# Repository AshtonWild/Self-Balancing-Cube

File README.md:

# Self-Balancing-Cube

**UPDATE (2026-11-11)**

You can print redesigned cube https://www.thingiverse.com/thing:6695891

Folow this video https://youtu.be/ZU0oTBRDgOE

---

I created a PCB with KiCad, as it was cleaner than using a prototype board and provided GERBER files for PCB Manufacturing in "Gerber".  I used JLCPCB to have the PCB built.

All parts are available via Digikey or AliExpress.  

CPU: ESP32 DEVKIT v1 Type-C

Battery: 3S1P LiPo 500 mAH (11.1V)

Motor: Nidec 24H brushless motors (8 Pin Required)

Other: Regulator (L7805), Transistor 2N2222, 5V Active Buzzer, Capacitor 100uF / 0.1uF, Register 6.8k / 33k / 10k

All red connections not nescesary for this project! But if you are designing a PCB I recommend making these connections. Maybe I use encoders in the future, you will be able to use the new firmware without any changes.
 
How to build:

https://youtu.be/AJQZFHJzwt4

If something doesn't work, try the motors test sketch. It tests all motors, rotation directions and speeds. This helps you understand the problem is in software or in hardware.

ESP32 version also has an updated balancing point setting procedure. Important! In this video you can learn how to set the balancing points:

https://youtu.be/Nkm9PoihZOI

# Self-Balancing Cube Calibration Manual

Calibrate in this order: sensor check, motor test, edge, then vertex. Each stage depends on the one before it, and nothing is kept until you type `save`.

## Before you start

- **Firmware**: the cube's Arduino code (ESP32, based on remrc's Self-Balancing-Cube), including the `watch` command and the automatic MPU6050 re-wake.
- **Console over USB**: Arduino Serial Monitor at **115200 baud**, line ending set to **New Line**. With "No line ending", commands never run.
- **Console over Bluetooth**: pair with **ESP32-Cube** and use any serial terminal app.
- **Chaining**: several commands can go on one line, separated by `;` (for example `zK2 8; zK3 0.3`).
- **Unsaved changes are lost** on every reboot and every upload. Type `save` once something works.
- **Safety**: keep fingers clear of the wheels. They can kick hard when balancing starts or a gain is wrong. Type `stop` at any time to brake the wheels, and `start` to re-enable them.

## Step 1: Power up and check the sensor

The sensor must give live readings before any calibration means anything. Our first vertex calibration was recorded while it read all zeros.

1. Power up with the cube **lying still**. The blue LED stays on for about 1 s while the gyro zeroes.  
   If the console says the cube moved, keep it still and type `gyrocal`.
2. Type `watch` (or `w`). You get a live line about 4 times a second, starting with `raw X … Y … Z …`.
3. Tilt the cube by hand. All three raw values must change. Lying flat, one of them reads about ±16384 (1 g).
4. Type `w off` to stop the live view.

If the raw values are all 0: the MPU6050 is powered but asleep, usually because it wasn't connected at boot. Type `reboot` with the cube still. The firmware now also re-wakes the sensor by itself and prints `MPU6050 found - woken up and configured`.

If you see `IMU read errors - check the MPU6050 wiring`: check SDA on GPIO 21, SCL on GPIO 22, VCC and GND, and that AD0 is low (address 0x68). If errors only appear when the motors run, keep the I2C wires short and away from the motor wires.

## Step 2: Check the battery and motors

1. **Battery (once)**: measure the pack with a multimeter and type the reading, for example `vcal 11.8`. This makes the battery value in `s` and the low-battery alarm (8 to 9.5 V) correct.  
   A 3S pack below about 11 V gives the wheels less top speed, so the cube falls sooner.
2. **Motors**: lay the cube on a side so the wheels spin freely, then type `mtest`. Each wheel spins for 0.6 s.  
   - **OK** for all three: continue.  
   - **encoder counts backwards**: swap `ENCx_1` and `ENCx_2` for that motor in the PINS section and re-upload.  
   - **not spinning**: check the battery and the BRAKE, DIR, PWM and encoder wiring.  
   Type `stop` at any point to abort the test and brake the wheels.

Don't continue until all three motors pass.

## Step 3: Calibrate the edge

The edge uses one motor (motor 3) and one tilt axis, so it's the easiest place to start. The original gains, eK1 190 and eK2 31, were correct: don't flip their signs.

1. Check the gains: type `eK1` and `eK2`. They should read 190 and 31. If not, type `defaults` (this keeps your calibration).
2. Record the balance point: type `cal e`. During the 3 s countdown, stand the cube on its edge and hold it lightly where it would fall neither way.  
   Run `watch` during the countdown to see the check: `|X|` must be 7000 to 10000 and `|Y|` below 2000, both marked `ok`.  
   Blue LED on = right position. Fast flicker = wrong position.  
   Hold still while it samples (about 1.5 s). LED on for 2 s = accepted; flicker = rejected, and the console says why.
3. Give it room: type `fall 10` so it doesn't cut out at 7° while you tune. Optionally type `arme 1` to make it start more easily.
4. Let it balance: stand it on the same edge. The console prints `Balancing on EDGE`.
5. Tune if it rocks: a slow, growing rock means it needs more damping. Change eK2 one step at a time and leave eK1 alone.  
   - Rocking gets smaller: keep going.  
   - Buzzing or jittering: one step too far, so back off.
6. Trim: while it balances on its own, type `autotrim` and don't touch it for about 9 s. Run it a second time. Our result was `te = −1.09`.
7. Save: type `save`. Then `reboot` and check it still balances on the edge.

## Step 4: Calibrate the vertex

The vertex worked with the original gains too: K1 180, K2 30, zK2 8, zK3 0.3. The step that fixed it was setting the balance-point trims by hand while watching the live tilt.

1. Check the gains: type `K1`, `K2`, `zK2` and `zK3`. They should read 180, 30, 8 and 0.3.
2. Record the balance point: type `cal v`. During the countdown, stand the cube on its corner and hold it lightly at its balance point.  
   In `watch`, `|X|` and `|Y|` must both be below 2000 and marked `ok`. The rotation must stay under 15 deg/s while it samples.
3. Make starting easier: type `armv 1`. With the default 0.4° window, it's very hard to start by hand.
4. Measure the offset with the motors off: type `stop`, then `watch`. Hold the cube at the point where it really balances (it would fall equally either way). Read the line, for example `vertex tilt X +2.10 off, Y -1.30 off`.
5. Set the trims: type `tvx` and `tvy` to see the current values. Add the readings to them: with both at 0 and the example above, that's `tvx 2.1; tvy -1.3`.
6. Check: at the real balance point, `watch` should now read close to `X +0.00 ok, Y +0.00 ok`.
7. Balance: type `start`, hold it at the balance point, and let go when it takes over. The console prints `Balancing on VERTEX`.
8. Trim: while it balances, run `autotrim` twice (about 9 s each, hands off).
9. Save: type `save`, then `reboot` and check both the corner and the edge still balance.

## Troubleshooting

Most problems we hit were the balance point or the sensor, not the gains. Change one thing at a time.

| Symptom | Cause | Fix |
|---------|-------|-----|
| Raw X, Y, Z all read 0 | MPU6050 asleep (not connected at boot) | `reboot` with the cube still |
| IMU read errors | I2C wiring or noise | Check SDA 21, SCL 22, power, AD0; short wires away from motors |
| Motors never start | Tilt outside armv / arme, motors stopped, or not calibrated | Read the `watch` line; `armv 1`, `start`, or `cal v` / `cal e` |
| `watch` never shows vertex tilt | Raw \|X\| at the corner is 2000 or more | Redo `cal v`; send the raw values if it persists |
| Falls at the real balance point, starts only when tilted further | Zero point recorded in the wrong spot | Set `tvx` / `tvy` by hand (Step 4) |
| Slow rock that grows until it falls | Too little damping | Nudge eK2 (edge) or K2 (vertex) one step at a time |
| Buzzing or fast jitter | Gains too high | Back off one step; try `dlpf 3` |
| Balances, then the wheels speed up and it falls | Small balance-point offset; wheels hit full speed | `autotrim`; or watch `ix` / `iy` in `tel 20` and nudge the trim until flat |
| Cube spins faster and faster around its vertical axis | Yaw gains wrong | Keep `zK2 8`; try `zK3 0.4` or `0.2`. `zK2 -8` made it much worse |
| Gains seem to change by themselves | Not saved before a reboot or upload | `save` after every change you want to keep |
| A command prints nothing | Line ending, baud, or output scrolled past | New Line, 115200, `w off`; `tel off`; type a name alone, e.g. `eK1` |

Flipping the gain signs (negative eK1 / eK2 or K1 / K2) did not help on this cube: the original positive values are correct.

## Reference

Working settings on this cube. Type `p` for the full list. Gains marked "default" come back with `defaults`; the others are saved with `save` only.

| Setting | Value | Notes |
|---------|-------|-------|
| eK1 / eK2 | 190 / 31 | Edge gains, default |
| te | −1.09 | Edge trim from `autotrim` |
| K1 / K2 | 180 / 30 | Vertex gains, default |
| zK2 / zK3 | 8 / 0.3 | Yaw gains, default |
| tvx / tvy | from Step 4 | Vertex trims, set by hand then `autotrim` |
| armv | 1 | Default 0.4; reset by `defaults` |
| fall | 10 | Default 7; set back with `fall 7` if you like |

## Console menu explained

Type `help` to show the menu on the cube. Commands aren't case-sensitive, short forms are in brackets, and `help <topic>` (for example `help cal` or `help K1`) gives more detail on any item.

### Info

| Command | What it does |
|---------|--------------|
| `help` (`?`, `menu`) | Shows the menu. `help <topic>` explains one command or setting in detail. |
| `help leds` | Explains the blue LED blink patterns and RGB colours (table below). |
| `status` (`s`) | One-screen health check: mode (IDLE, VERTEX or EDGE), motors enabled or stopped, which position the cube is in, battery volts, angles, raw sensor values, wheel speeds and loop timing. Worst period should stay near 15000 us; late and I2C errors should stay at 0. |
| `params` (`p`) | Lists every tunable value, its current setting and what it does. Says if there are unsaved changes. |
| `tel [hz]` / `tel off` | Streams live data for the Arduino Serial Plotter (Tools > Serial Plotter). Default 20 Hz, maximum 66; keep it at 20 Hz or less over Bluetooth. Fields: m mode (0 idle, 1 vertex, 2 edge), ax ay tilt angle, gx gy tilt rate, w1–w3 wheel speeds, px py pz motor output (−255 to 255), ix iy wheel-position term. A steady ramp in ix or iy means the balance point is off. |
| `watch [hz]` (`w`) / `w off` | Readable live guide, default 4 Hz. Shows the raw sensor values and what's in or out of range: the calibration windows during `cal`, or the tilt from the balance point and the start window otherwise. Notes `[motors STOPPED]` when the wheels are off. |

### Setup and calibration

| Command | What it does |
|---------|--------------|
| `mtest` | Motor and encoder test, about 3 s. Lay the cube on a side first. Spins each wheel for 0.6 s and reports OK, backwards (swap that motor's encoder pins) or not spinning (check power and wiring). Won't start while the motors are stopped; `stop` aborts it. |
| `cal v [sec]` | Records the vertex balance point after a countdown (default 3 s). Needs raw \|X\| and \|Y\| below 2000 and rotation under 15 deg/s. Resets the vertex trims to 0. |
| `cal e [sec]` | Records the edge balance point the same way. Needs raw \|X\| of 7000 to 10000 and \|Y\| below 2000. Resets the edge trim to 0. |
| `autotrim` | Run while the cube balances on its own. Averages the lean for about 9 s and moves the trims (`tvx` / `tvy` on the vertex, `te` on the edge) to the real balance point. Run it twice, then `save`. Aborts if the cube stops balancing. |
| `gyrocal [sec]` | Re-zeroes the gyro (also done automatically at power-up). Keep the cube still; rejected if it moves. Use it if the angle drifts while the cube sits still. |
| `vcal <volts>` | Type a multimeter reading of the battery, e.g. `vcal 11.8`, to make the battery value and low-battery alarm correct. Rejects readings that don't make sense (for example a disconnected divider). |
| `buzz` | Two-part buzzer test. Test 1 (steady on): an active buzzer beeps. Test 2 (2 kHz tone): a passive buzzer beeps. The project needs an active 5 V buzzer. Silent in both: check polarity, 5 V and the transistor on GPIO 27. |

### Tuning

| Command | What it does |
|---------|--------------|
| `<name> <value>` | Sets a value, e.g. `K1 185`. Also works as `set K1 185` or `K1=185`. Values outside the allowed range are limited. |
| `<name>` | Prints one value, e.g. `eK2`. |
| `<name>+` / `<name>-` | Nudges a value by one step; repeat the sign for more steps (`eK3+++`). |

| Setting | What it controls | Default | Range (step) |
|---------|------------------|---------|--------------|
| K1 | Vertex: angle gain | 180 | −2000 to 2000 (5) |
| K2 | Vertex: tilt-rate gain (damping) | 30 | −500 to 500 (1) |
| K3 | Vertex: wheel-speed gain | 1.6 | −50 to 50 (0.1) |
| K4 | Vertex: wheel-position gain | 0.008 | −1 to 1 (0.001) |
| zK2 | Vertex: yaw-rate gain (stops turning) | 8 | −100 to 100 (0.5) |
| zK3 | Vertex: yaw wheel-speed gain | 0.3 | −10 to 10 (0.05) |
| eK1 | Edge: angle gain | 190 | −2000 to 2000 (5) |
| eK2 | Edge: tilt-rate gain (damping) | 31 | −500 to 500 (1) |
| eK3 | Edge: wheel-speed gain | 2.5 | −50 to 50 (0.1) |
| eK4 | Edge: wheel-position gain | 0.014 | −1 to 1 (0.001) |
| tvx / tvy | Vertex trims, degrees | 0 (set by `cal v`) | −5 to 5 (0.05) |
| te | Edge trim, degrees | 0 (set by `cal e`) | −5 to 5 (0.05) |
| gyroamt | How much the angle trusts the gyro over the accelerometer | 0.996 | 0.9 to 0.9999 (0.001) |
| alpha | Tilt-rate smoothing (1 = off) | 0.7 | 0.05 to 1 (0.05) |
| armv | Vertex: starts balancing within this angle, degrees | 0.4 | 0.1 to 5 (0.1) |
| arme | Edge: starts balancing within this angle, degrees | 0.3 | 0.1 to 5 (0.1) |
| fall | Stops balancing above this tilt, degrees | 7 | 2 to 20 (0.5) |
| vdiv | Battery ADC counts per volt (set by `vcal`) | 204 | 50 to 1000 (1) |
| dlpf | MPU6050 filter: 0 = 260 Hz, 1 = 184, 2 = 94, 3 = 44, 4 = 21 | 0 | 0 to 6 (1) |

### Motors and settings

| Command | What it does |
|---------|--------------|
| `stop` / `start` | `stop` brakes the wheels and keeps them off (and cancels a countdown or motor test) until `start`. Settings aren't affected. |
| `save` | Writes all settings and calibration to flash. Changes work straight away but are lost on reboot until saved. |
| `load` | Re-reads flash, undoing anything not yet saved. |
| `defaults` | Puts back the original gains, filters and start/stop angles. Keeps calibration, trims and vdiv. Type `save` to keep it. |
| `factory` | Erases everything including calibration, and saves immediately. The cube must be lying down. |
| `reboot` | Restarts the ESP32. Keep the cube still afterwards while the gyro zeroes. |

## LED meanings

The optional RGB LEDs on GPIO 19 show the same states in colour: green = good, red = problem, yellow = sampling or getting close, purple = not calibrated, cyan = motor test, dim green = balancing, dim red = stopped.

| Blue LED (GPIO 2) | Meaning |
|-------------------|---------|
| On at power-up | Zeroing the gyro: keep the cube still |
| Double blink | Not calibrated yet |
| On during a `cal` countdown | Right position |
| Fast flicker during a countdown | Wrong position |
| Steady blinking while sampling | Hold still |
| On for 2 s after a job | Accepted |
| Fast flicker for 2 s after a job | Rejected (the console says why) |
| Slow / quicker blink / on, when ready | Within 5° / 2.5° / 1° of the balance point |
| On | Balancing |
| Short blip every 2 s | Motors stopped (type `start`) |
| Slow blink | Motor test, or a `gyrocal` / `mtest` countdown |

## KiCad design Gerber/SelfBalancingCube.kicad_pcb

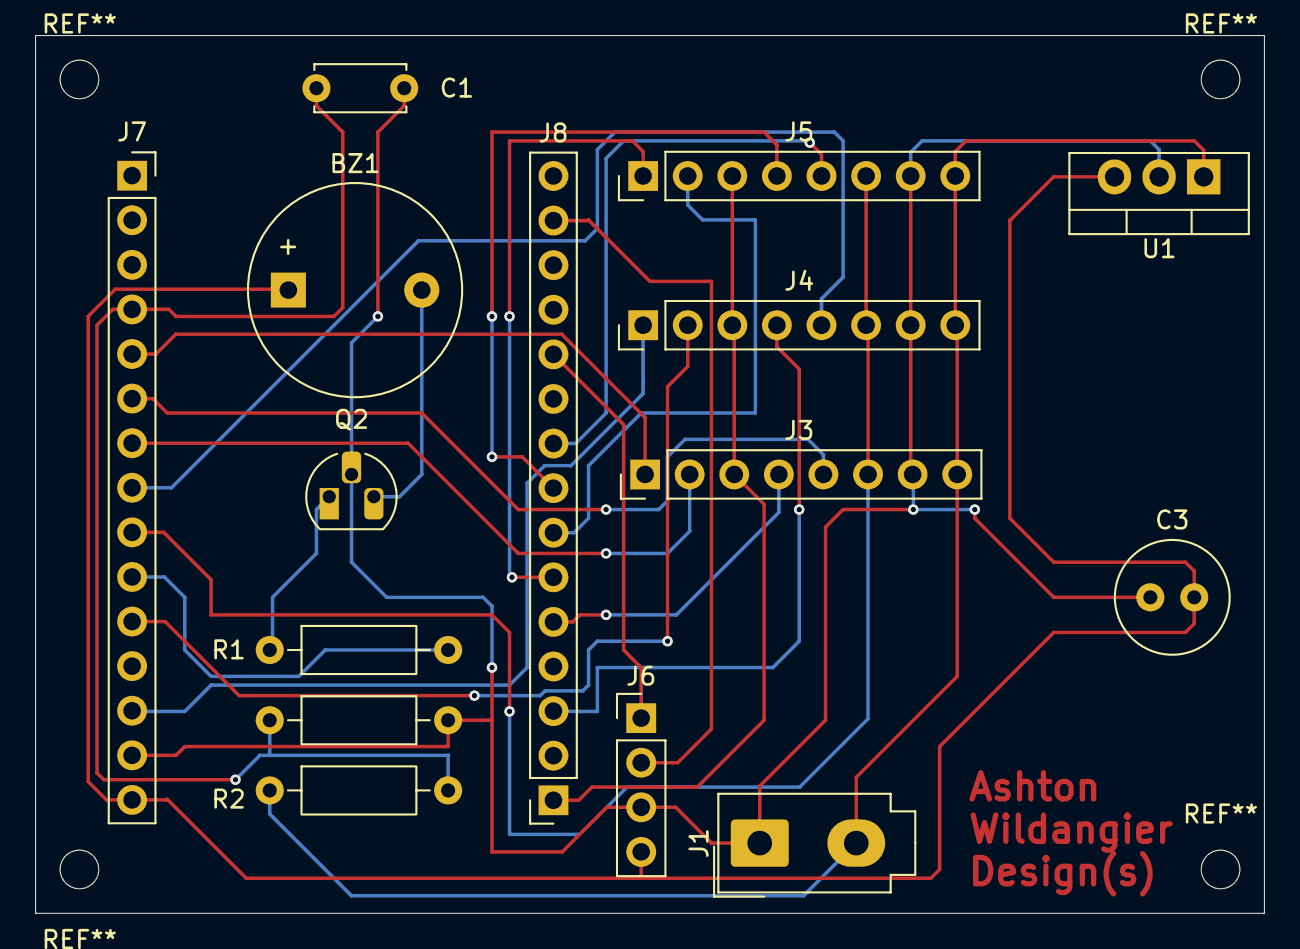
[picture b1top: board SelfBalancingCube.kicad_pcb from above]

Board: 2 copper layers, 70.0 x 50.0 mm, 15 parts (0 on the bottom side), 23 nets.

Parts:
BZ1: Buzzer; Buzzer_12x9.5RM7.6
C1: C_Small_US; C_Disc_D5.0mm_W2.5mm_P5.00mm
C3: 100uF; C_Radial_D6.3mm_H7.0mm_P2.50mm
J1: Conn_01x02; Molex_Mini-Fit_Jr_5566-02A_2x01_P4.20mm_Vertical
J3, J4, J5: Nidec 24H; PinHeader_1x08_P2.54mm_Vertical
J6: Conn_01x04_Pin; PinHeader_1x04_P2.54mm_Vertical
J7, J8: Conn_01x15_Socket; PinSocket_1x15_P2.54mm_Vertical
Q2: PN2222A; TO-92_HandSolder
R1: 6.8K; R_Axial_DIN0207_L6.3mm_D2.5mm_P10.16mm_Horizontal
R2: 33K; R_Axial_DIN0207_L6.3mm_D2.5mm_P10.16mm_Horizontal
R3: 1OK; R_Axial_DIN0207_L6.3mm_D2.5mm_P10.16mm_Horizontal
U1: L7805; TO-220-3_Vertical

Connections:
unnamed: BZ1.1 (+), C3.2, J6.4, J7.15, U1.3 (OUT)
unnamed: BZ1.2 (-), Q2.3 (C)
unnamed: C1.2, C3.1, J1.1, J3.7, J4.7, J5.7, J6.3, J7.14, Q2.2 (B), R3.2, U1.2 (GND)
unnamed: J1.2, J3.8, J4.8, J5.8, R2.1, U1.1 (IN)
unnamed: J3.1, J7.5
unnamed: J3.2, J7.7
unnamed: J3.3, J4.3, J5.3, J8.1
unnamed: J3.4, J8.5
unnamed: J3.5, J7.6
unnamed: J3.6, J4.6, J5.6, J7.9
unnamed: J4.1, J7.13
unnamed: J4.2, J7.11
unnamed: J4.4, J8.3
unnamed: J4.5, J7.8
unnamed: J5.1, J8.6
unnamed: J5.2, J8.7
unnamed: J5.4, J8.8
unnamed: J5.5, J8.9
unnamed: J6.1, J8.11
unnamed: J6.2, J8.14
unnamed: C1.1, J7.4, R2.2, R3.1
unnamed: J7.10, R1.2
unnamed: Q2.1 (E), R1.1
